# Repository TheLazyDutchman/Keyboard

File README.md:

# Ferry
I have tried to make my own custom keyboard, using [ergogen](https://ergogen.xyz/) to generate all the usefull files from a few simple configs.

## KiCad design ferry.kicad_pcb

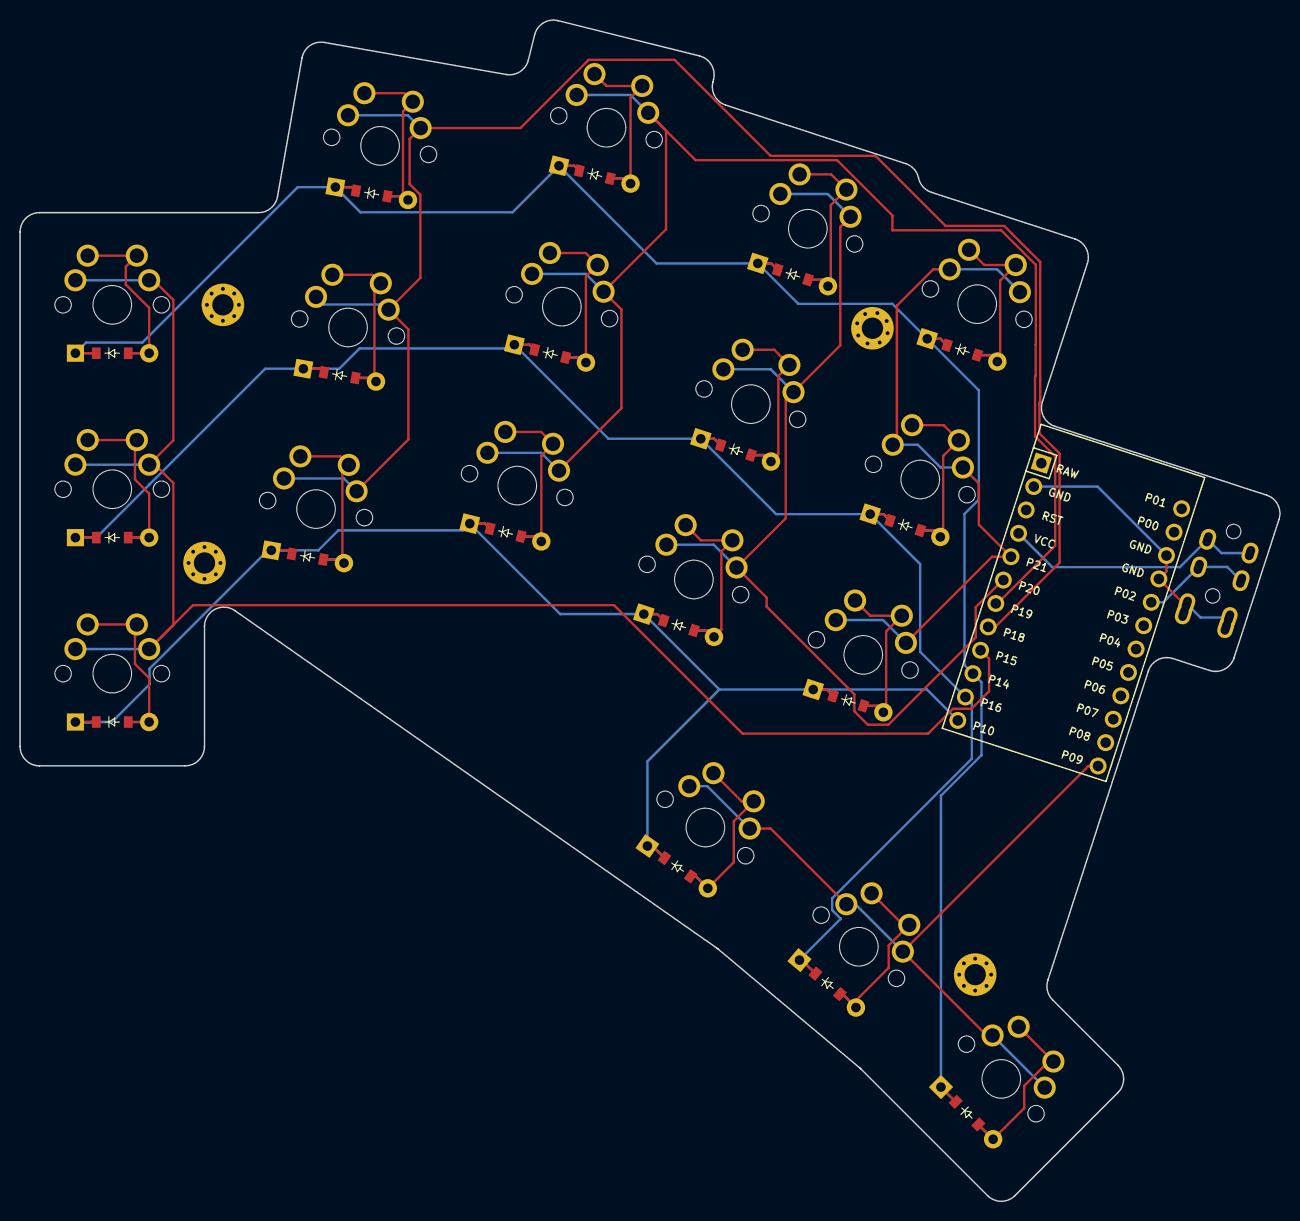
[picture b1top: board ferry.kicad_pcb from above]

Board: 2 copper layers, 130.2 x 122.0 mm, 42 parts (0 on the bottom side), 30 nets.

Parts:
D1, D2, D3, D4, D5, D6, D7, D8, D9, D10, D11, D12, D13, D14, D15, D16, D17, D18: ComboDiode
MCU1: ProMicro
S1, S2, S3, S4, S5, S6, S7, S8, S9, S10, S11, S12, S13, S14, S15, S16, S17, S18: MX
TRRS1: TRRS-PJ-320A-dual
_1, _2, _3, _4: MountingHole_2.2mm_M2_Pad_Via

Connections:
GND: MCU1.2, MCU1.15, MCU1.16, TRRS1.1, TRRS1.2
P2: MCU1.17, TRRS1.3
P9: MCU1.24, S16.2, S17.2, S18.2
P10: D1.1, D4.1, D7.1, D10.1, D13.1, D16.1, MCU1.12
P14: D3.1, D6.1, D9.1, D12.1, D15.1, D18.1, MCU1.10
P15: MCU1.9, S1.2, S2.2, S3.2
P16: D2.1, D5.1, D8.1, D11.1, D14.1, D17.1, MCU1.11
P18: MCU1.8, S4.2, S5.2, S6.2
P19: MCU1.7, S7.2, S8.2, S9.2
P20: MCU1.6, S10.2, S11.2, S12.2
P21: MCU1.5, S13.2, S14.2, S15.2
VCC: MCU1.4, TRRS1.4
home_row: D17.2, S17.1
index_bottom: D10.2, S10.1
index_home: D11.2, S11.1
index_top: D12.2, S12.1
middle_bottom: D7.2, S7.1
middle_home: D8.2, S8.1
middle_top: D9.2, S9.1
outer_bottom: D13.2, S13.1
outer_home: D14.2, S14.1
outer_top: D15.2, S15.1
pinky_bottom: D1.2, S1.1
pinky_home: D2.2, S2.1
pinky_top: D3.2, S3.1
reach_row: D18.2, S18.1
ring_bottom: D4.2, S4.1
ring_home: D5.2, S5.1
ring_top: D6.2, S6.1
tuck_row: D16.2, S16.1

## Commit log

2024-01-07 Traced final pcb
2024-01-08 Updated layout
